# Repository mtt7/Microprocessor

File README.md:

# Power Supply
Custom made microprocessor PCB board

## Folder structure

### Hardware
Contains KiCAD files, schematics, pcb design, libraries.

### Simulation
Contains simulation files for logisim 2.7.1.

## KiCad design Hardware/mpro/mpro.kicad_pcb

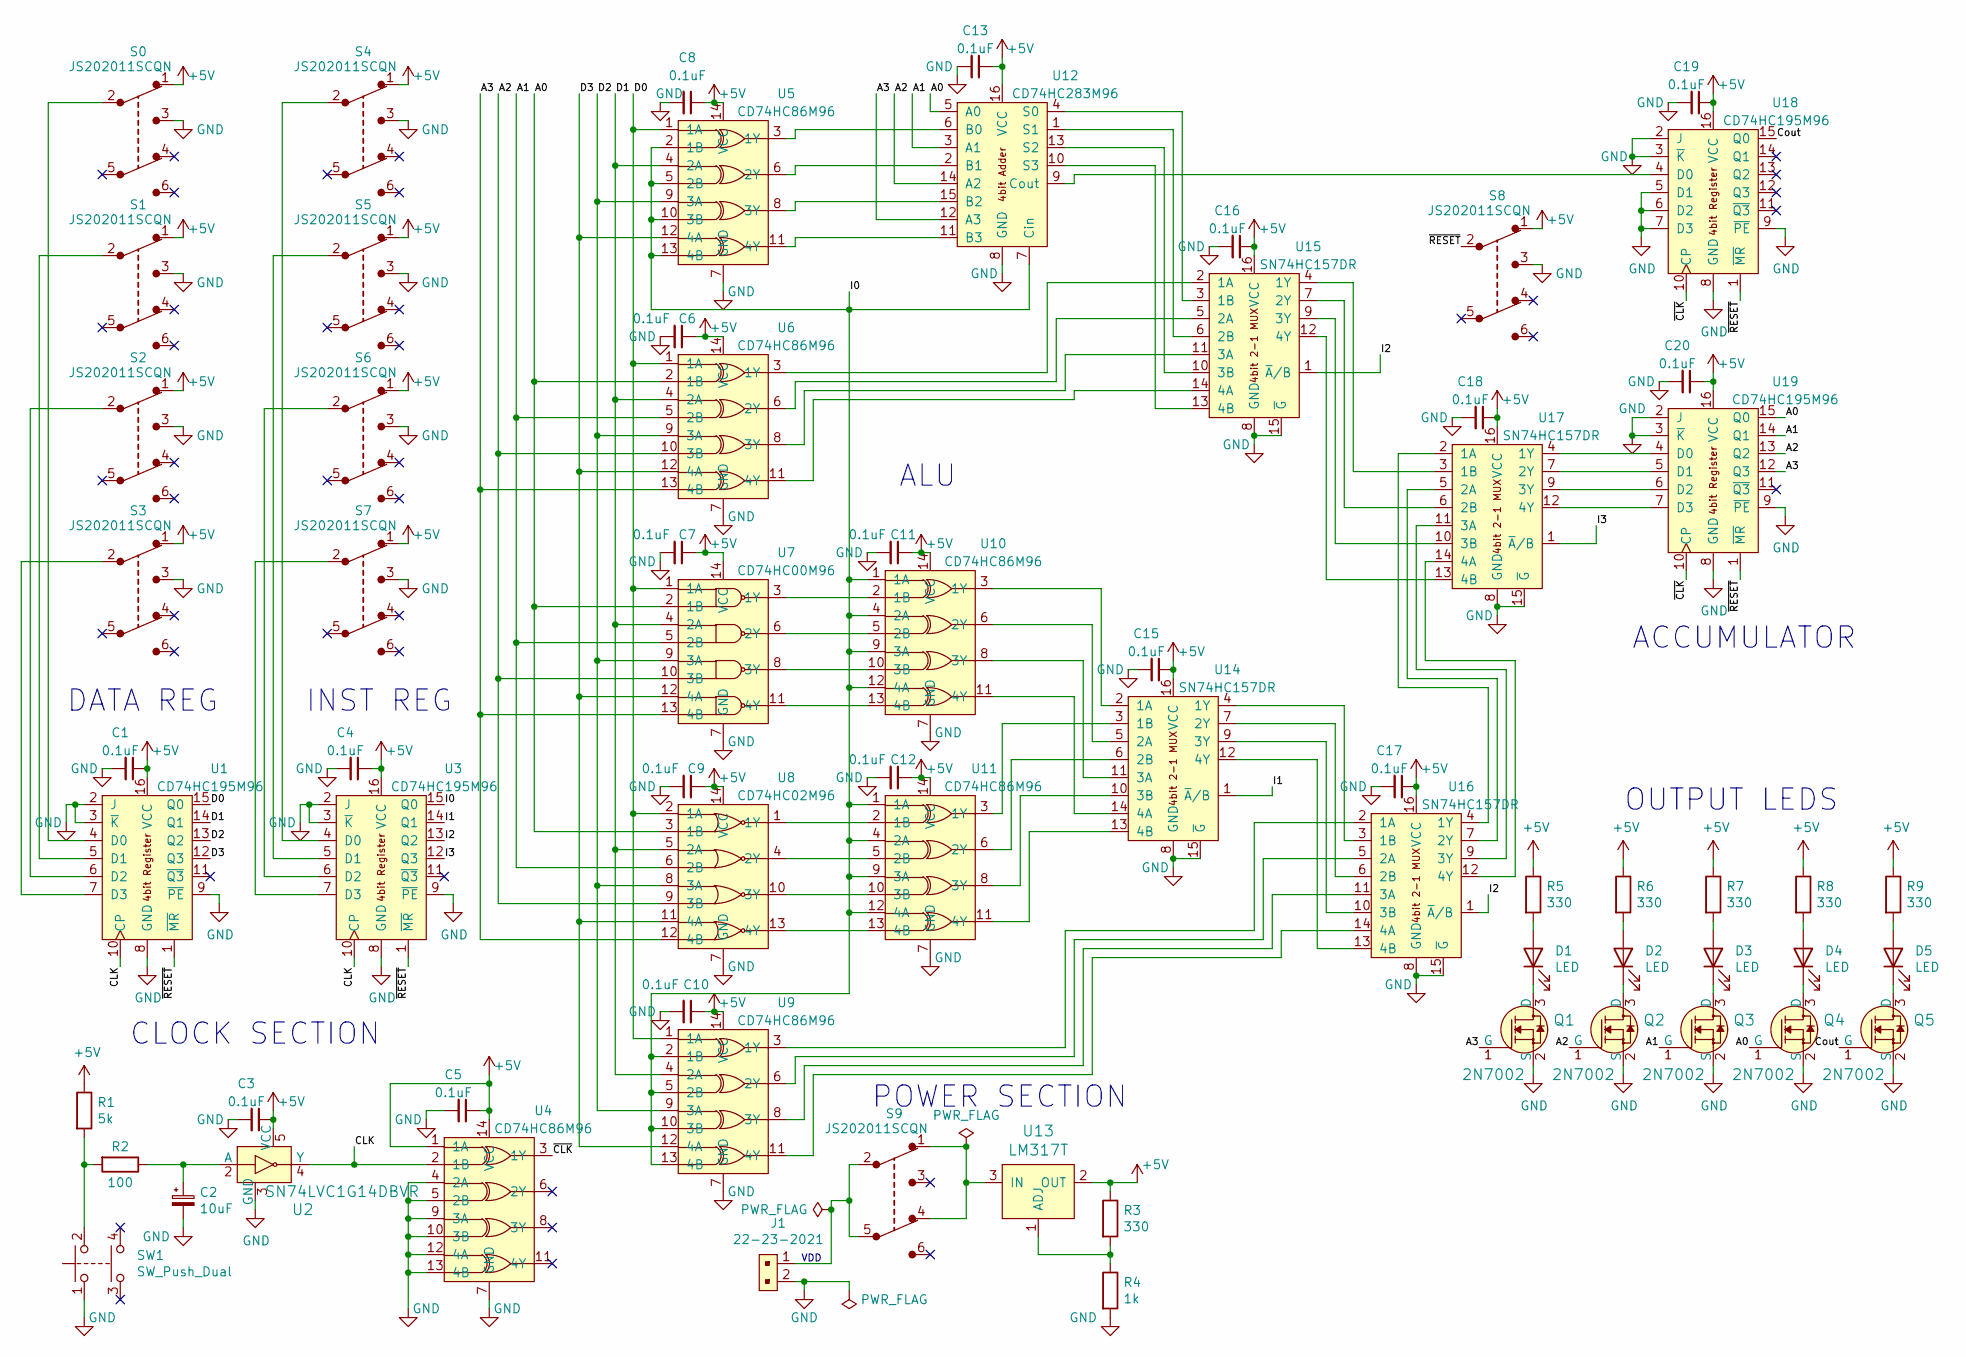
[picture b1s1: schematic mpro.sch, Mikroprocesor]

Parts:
C1, C3, C4, C5, C6, C7, C8, C9, C10, C11, C12, C13, C15, C16, C17, C18, C19, C20: 0.1uF; C_Disc_D3.0mm_W2.0mm_P2.50mm
C2: 10uF; CP_Radial_D4.0mm_P2.00mm
D1, D2, D3, D4, D5: LED; LED_D8.0mm
J1: 22-23-2021; PinHeader_1x2_P2.54mm_Drill1.02mm; MPN 22-23-2021; Digi-Key_PN WM4200-ND
Q1, Q2, Q3, Q4, Q5: 2N7002; SOT-23-3; MPN 2N7002; Digi-Key_PN 2N7002NCT-ND
R1: 5k; R_Axial_DIN0207_L6.3mm_D2.5mm_P15.24mm_Horizontal
R2: 100; R_Axial_DIN0207_L6.3mm_D2.5mm_P15.24mm_Horizontal
R3, R5, R6, R7, R8, R9: 330; R_Axial_DIN0207_L6.3mm_D2.5mm_P15.24mm_Horizontal
R4: 1k; R_Axial_DIN0207_L6.3mm_D2.5mm_P15.24mm_Horizontal
S0, S1, S2, S3, S4, S5, S6, S7, S8, S9: JS202011SCQN; Switch_Slide_JS202011SCQN; MPN JS202011SCQN; Digi-Key_PN 401-2002-1-ND
SW1: SW_Push_Dual; SW_PUSH_6mm
U1, U3, U18, U19: CD74HC195M96; SOIC-16_3.9x9.9mm_P1.27mm
U2: SN74LVC1G14DBVR; SOT-753; MPN SN74LVC1G14DBVR; Digi-Key_PN 296-11607-1-ND
U4, U5, U6, U9, U10, U11: CD74HC86M96; SOIC-14_3.9x8.7mm_P1.27mm
U7: CD74HC00M96; SOIC-14_3.9x8.7mm_P1.27mm
U8: CD74HC02M96; SOIC-14_3.9x8.7mm_P1.27mm
U12: CD74HC283M96; SOIC-16_3.9x9.9mm_P1.27mm
U13: LM317T; TO-220-3; MPN LM317T; Digi-Key_PN 497-1575-5-ND
U14, U15, U16, U17: SN74HC157DR; SOIC-16_3.9x9.9mm_P1.27mm

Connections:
+5V: C1.1, C3.1, C4.1, C5.1, C6.1, C7.1, C8.1, C9.1, C10.1, C11.1, C12.1, C13.1, C15.1, C16.1, C17.1, C18.1, C19.1, C20.1, R1.1, R3.1, R5.1, R6.1, R7.1, R8.1, R9.1, S0.1, S1.1, S2.1, S3.1, S4.1, S5.1, S6.1, S7.1, S8.1, U1.16 (VCC), U2.5 (VCC), U3.16 (VCC), U4.1 (1A), U4.14 (VCC), U5.14 (VCC), U6.14 (VCC), U7.14 (VCC), U8.14 (VCC), U9.14 (VCC), U10.14 (VCC), U11.14 (VCC), U12.16 (VCC), U13.2 (OUT), U14.16 (VCC), U15.16 (VCC), U16.16 (VCC), U17.16 (VCC), U18.16 (VCC), U19.16 (VCC)
/A0: Q4.1 (G), U6.2 (1B), U7.2 (1B), U8.3 (1B), U12.5 (A0), U19.15 (Q0)
/A1: Q3.1 (G), U6.5 (2B), U7.5 (2B), U8.6 (2B), U12.3 (A1), U19.14 (Q1)
/A2: Q2.1 (G), U6.10 (3B), U7.10 (3B), U8.9 (3B), U12.14 (A2), U19.13 (Q2)
/A3: Q1.1 (G), U6.13 (4B), U7.13 (4B), U8.12 (4B), U12.12 (A3), U19.12 (Q3)
/CLK: U1.10 (CP), U2.4 (Y), U3.10 (CP), U4.2 (1B)
/Cout: Q5.1 (G), U18.15 (Q0)
/D0: U1.15 (Q0), U5.1 (1A), U6.1 (1A), U7.1 (1A), U8.2 (1A), U9.1 (1A)
/D1: U1.14 (Q1), U5.4 (2A), U6.4 (2A), U7.4 (2A), U8.5 (2A), U9.4 (2A)
/D2: U1.13 (Q2), U5.9 (3A), U6.9 (3A), U7.9 (3A), U8.8 (3A), U9.9 (3A)
/D3: U1.12 (Q3), U5.12 (4A), U6.12 (4A), U7.12 (4A), U8.11 (4A), U9.12 (4A)
/I0: U3.15 (Q0), U5.2 (1B), U5.5 (2B), U5.10 (3B), U5.13 (4B), U9.2 (1B), U9.5 (2B), U9.10 (3B), U9.13 (4B), U10.1 (1A), U10.4 (2A), U10.9 (3A), U10.12 (4A), U11.1 (1A), U11.4 (2A), U11.9 (3A), U11.12 (4A), U12.7 (Cin)
/I1: U3.14 (Q1), U14.1 (~A~/B)
/I2: U3.13 (Q2), U15.1 (~A~/B), U16.1 (~A~/B)
/I3: U3.12 (Q3), U17.1 (~A~/B)
/~CLK~: U4.3 (1Y), U18.10 (CP), U19.10 (CP)
/~RESET~: S8.2, U1.1 (~MR~), U3.1 (~MR~), U18.1 (~MR~), U19.1 (~MR~)
GND: C1.2, C2.2, C3.2, C4.2, C5.2, C6.2, C7.2, C8.2, C9.2, C10.2, C11.2, C12.2, C13.2, C15.2, C16.2, C17.2, C18.2, C19.2, C20.2, J1.2, Q1.2 (S), Q2.2 (S), Q3.2 (S), Q4.2 (S), Q5.2 (S), R4.2, S0.3, S1.3, S2.3, S3.3, S4.3, S5.3, S6.3, S7.3, S8.3, SW1.1, U1.2 (J), U1.3 (~K~), U1.8 (GND), U1.9 (~PE~), U2.3 (GND), U3.2 (J), U3.3 (~K~), U3.8 (GND), U3.9 (~PE~), U4.4 (2A), U4.5 (2B), U4.7 (GND), U4.9 (3A), U4.10 (3B), U4.12 (4A), U4.13 (4B), U5.7 (GND), U6.7 (GND), U7.7 (GND), U8.7 (GND), U9.7 (GND), U10.7 (GND), U11.7 (GND), U12.8 (GND), U14.8 (GND), U14.15 (~G~), U15.8 (GND), U15.15 (~G~), U16.8 (GND), U16.15 (~G~), U17.8 (GND), U17.15 (~G~), U18.2 (J), U18.3 (~K~), U18.5 (D1), U18.6 (D2), U18.7 (D3), U18.8 (GND), U18.9 (~PE~), U19.2 (J), U19.3 (~K~), U19.8 (GND), U19.9 (~PE~)
unnamed: C2.1, R2.1, U2.2 (A)
unnamed: D1.1 (K), Q1.3 (D)
unnamed: D1.2 (A), R5.2
unnamed: D2.1 (K), Q2.3 (D)
unnamed: D2.2 (A), R6.2
unnamed: D3.1 (K), Q3.3 (D)
unnamed: D3.2 (A), R7.2
unnamed: D4.1 (K), Q4.3 (D)
unnamed: D4.2 (A), R8.2
unnamed: D5.1 (K), Q5.3 (D)
unnamed: D5.2 (A), R9.2
unnamed: J1.1, S9.2, S9.5
unnamed: R1.2, R2.2, SW1.2
unnamed: R3.2, R4.1, U13.1 (ADJ)
unnamed: S0.2, U1.4 (D0)
unnamed: S1.2, U1.5 (D1)
unnamed: S2.2, U1.6 (D2)
unnamed: S3.2, U1.7 (D3)
unnamed: S4.2, U3.4 (D0)
unnamed: S5.2, U3.5 (D1)
unnamed: S6.2, U3.6 (D2)
unnamed: S7.2, U3.7 (D3)
unnamed: S9.1, S9.4, U13.3 (IN)
unnamed: U7.3 (1Y), U10.2 (1B)
unnamed: U10.3 (1Y), U14.2 (1A)
unnamed: U7.6 (2Y), U10.5 (2B)
unnamed: U10.6 (2Y), U14.5 (2A)
unnamed: U10.8 (3Y), U14.11 (3A)
unnamed: U7.8 (3Y), U10.10 (3B)
unnamed: U10.11 (4Y), U14.14 (4A)
unnamed: U7.11 (4Y), U10.13 (4B)
unnamed: U8.1 (1Y), U11.2 (1B)
unnamed: U11.3 (1Y), U14.3 (1B)
unnamed: U8.4 (2Y), U11.5 (2B)
unnamed: U11.6 (2Y), U14.6 (2B)
unnamed: U11.8 (3Y), U14.10 (3B)
unnamed: U8.10 (3Y), U11.10 (3B)
unnamed: U11.11 (4Y), U14.13 (4B)
unnamed: U8.13 (4Y), U11.13 (4B)
unnamed: U12.1 (S1), U15.6 (2B)
unnamed: U5.6 (2Y), U12.2 (B1)
unnamed: U12.4 (S0), U15.3 (1B)
unnamed: U5.3 (1Y), U12.6 (B0)
unnamed: U12.9 (Cout), U18.4 (D0)
unnamed: U12.10 (S3), U15.13 (4B)
unnamed: U5.11 (4Y), U12.11 (B3)
unnamed: U12.13 (S2), U15.10 (3B)
unnamed: U5.8 (3Y), U12.15 (B2)
unnamed: U14.4 (1Y), U16.3 (1B)
unnamed: U14.7 (2Y), U16.6 (2B)
unnamed: U14.9 (3Y), U16.10 (3B)
unnamed: U14.12 (4Y), U16.13 (4B)
unnamed: U6.3 (1Y), U15.2 (1A)
unnamed: U15.4 (1Y), U17.3 (1B)
unnamed: U6.6 (2Y), U15.5 (2A)
unnamed: U15.7 (2Y), U17.6 (2B)
unnamed: U15.9 (3Y), U17.10 (3B)
unnamed: U6.8 (3Y), U15.11 (3A)
unnamed: U15.12 (4Y), U17.13 (4B)
unnamed: U6.11 (4Y), U15.14 (4A)
unnamed: U9.3 (1Y), U16.2 (1A)
unnamed: U16.4 (1Y), U17.2 (1A)
unnamed: U9.6 (2Y), U16.5 (2A)
unnamed: U16.7 (2Y), U17.5 (2A)
unnamed: U16.9 (3Y), U17.11 (3A)
unnamed: U9.8 (3Y), U16.11 (3A)
unnamed: U16.12 (4Y), U17.14 (4A)
unnamed: U9.11 (4Y), U16.14 (4A)
unnamed: U17.4 (1Y), U19.4 (D0)
unnamed: U17.7 (2Y), U19.5 (D1)
unnamed: U17.9 (3Y), U19.6 (D2)
unnamed: U17.12 (4Y), U19.7 (D3)

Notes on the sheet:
VDD
POWER SECTION
ALU
ACCUMULATOR
OUTPUT LEDS
DATA REG
INST REG
CLOCK SECTION

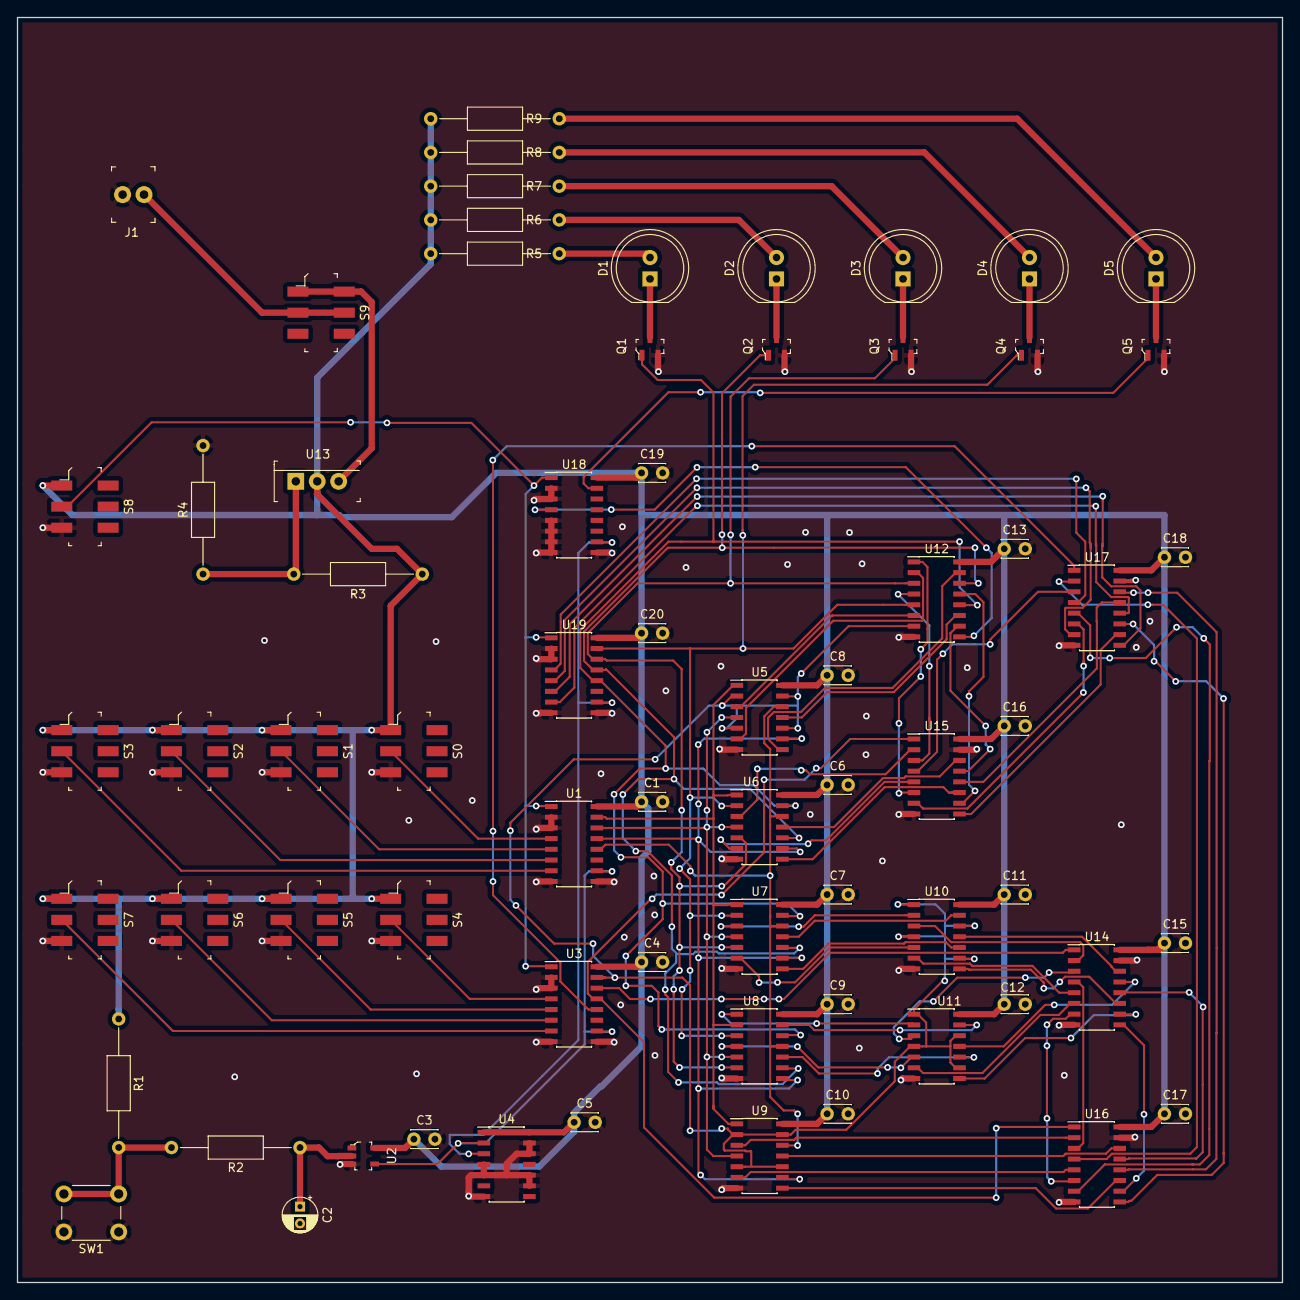
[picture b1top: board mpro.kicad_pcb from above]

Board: 2 copper layers, 150.0 x 150.0 mm, 69 parts (0 on the bottom side), 90 nets.
